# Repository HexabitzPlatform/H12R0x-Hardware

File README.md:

# H12R0x-Hardware
Hexabitz Industrial 12-Bit Analog Input ±10 V Module Hardware Design

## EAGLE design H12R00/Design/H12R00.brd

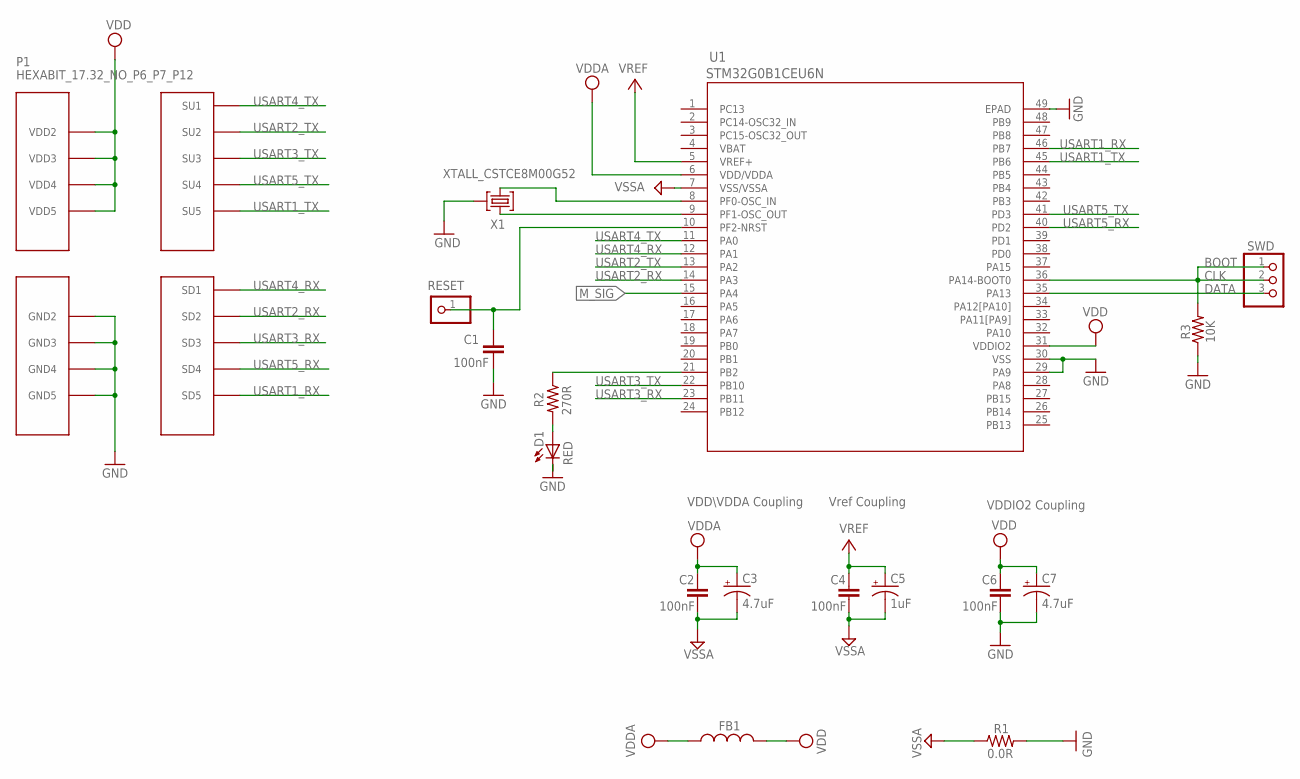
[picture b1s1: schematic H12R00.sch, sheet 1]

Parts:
C1, C2, C4, C6: 100nF; C-0603
C3, C7: 4.7uF; C-0805-POL
C5: 1uF; C-0805-POL
D1: RED; VLMS1300-GS08; MPN VLMS1300-GS08
FB1: FB-0603
P1: HEXABIT_17.32_NO_P6_P7_P12
R1: 0.0R; R-0603
R2: 270R; R-0603
R3: 10K; R-0603
RESET: R; 1X01
SWD: PINHD-1X3SWD; SWD
U1: STM32G0B1CEU6N; HEXABITZ_ICS_QFN_B1CEU6_STM-L
X1: XTALL_CSTCE8M00G52

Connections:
CLK: R3.2, SWD.1, SWD.2, U1.36 (PA14-BOOT0)
DATA: SWD.3, U1.35 (PA13)
GND: C1.2, C6.2, C7.2 (-), D1.C, P1.PAD_PD8 (GND2), P1.PAD_PD9 (GND3), P1.PAD_PD10 (GND4), P1.PAD_PD11 (GND5), R1.2, R3.1, U1.29 (PA9), U1.30 (VSS), U1.49 (EPAD), X1.P$2 (2)
M_SIG: U1.15 (PA4); also elsewhere on the board
unnamed: D1.A, R2.2
unnamed: R2.1, U1.21 (PB2)
unnamed: U1.9 (PF1-OSC_OUT), X1.P$1 (1)
unnamed: U1.8 (PF0-OSC_IN), X1.P$3 (3)
unnamed: C1.1, RESET.1, U1.10 (PF2-NRST)
USART1_RX: P1.PAD_PD5 (SD5), U1.46 (PB7)
USART1_TX: P1.PAD_PU5 (SU5), U1.45 (PB6)
USART2_RX: P1.PAD_PD2 (SD2), U1.14 (PA3)
USART2_TX: P1.PAD_PU2 (SU2), U1.13 (PA2)
USART3_RX: P1.PAD_PD3 (SD3), U1.23 (PB11)
USART3_TX: P1.PAD_PU3 (SU3), U1.22 (PB10)
USART4_RX: P1.PAD_PD1 (SD1), U1.12 (PA1)
USART4_TX: P1.PAD_PU1 (SU1), U1.11 (PA0)
USART5_RX: P1.PAD_PD4 (SD4), U1.40 (PD2)
USART5_TX: P1.PAD_PU4 (SU4), U1.41 (PD3)
VBAT: U1.4 (VBAT)
VDD: C6.1, C7.1 (+), FB1.2, P1.PAD_PU8 (VDD2), P1.PAD_PU9 (VDD3), P1.PAD_PU10 (VDD4), P1.PAD_PU11 (VDD5), U1.31 (VDDIO2)
VDDA: C2.1, C3.1 (+), FB1.1, U1.6 (VDD/VDDA); also elsewhere on the board
VREF: C4.1, C5.1 (+), U1.5 (VREF+); also elsewhere on the board
VSSA: C2.2, C3.2 (-), C4.2, C5.2 (-), R1.1, U1.7 (VSS/VSSA); also elsewhere on the board

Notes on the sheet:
Vref Coupling
VDDIO2 Coupling
VDD\VDDA Coupling
BOOT

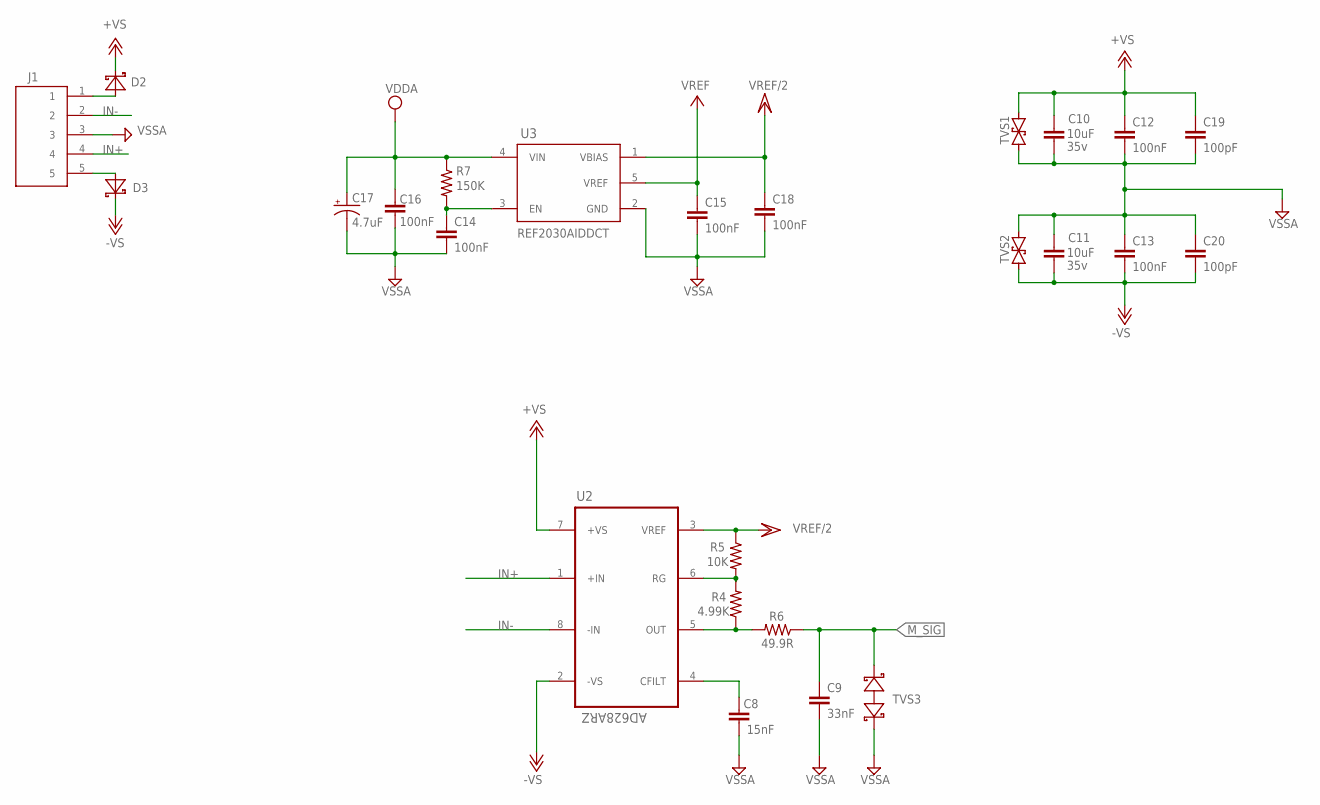
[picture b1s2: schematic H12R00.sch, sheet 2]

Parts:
C8: 15nF; C-0603
C9: 33nF; C-0603
C10, C11: C-0805; VOLTAGE_RATING 35v; MPN GRM21BR6YA106ME43K
C12, C13: 100nF; C-0603; MPN C1608X7R1H104K080AA
C14, C15, C16, C18: 100nF; C-0603
C17: 4.7uF; C-0805-POL
C19, C20: 100pF; C-0603; MPN C1608X7R1H104K080AA
D2, D3: DIOD-SOD-123; SOD123
J1: 1984646
R4: 4.99K; R-0603
R5: 10K; R-0603
R6: 49.9R; R-0603
R7: 150K; R-0603
TVS1, TVS2: SMBJ30CA; DO214AA
TVS3: BOURNS_CDSOD323-T03SCBOURNS_CDSOD323-T03SC_0_0; BOURNS_CDSOD323-T03SC_0
U2: AD628ARZ; SOIC127P600X175-8N
U3: TEXAS_INSTRUMENTS_REF2033AIDDCRTEXAS_INSTRUMENTS_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; TEXAS_INSTRUMENTS_REF2033AIDDCR_2; MPN REF2030AIDDCT

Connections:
+VS: C10.1, C12.1, C19.1, D2.2 (C), TVS1.C (2), U2.7 (+VS)
-VS: C11.2, C13.2, C20.2, D3.2 (C), TVS2.A (1), U2.2 (-VS)
CFILT: C8.1, U2.4 (CFILT)
IN+: J1.4, U2.1 (+IN)
IN-: J1.2, U2.8 (-IN)
M_SIG: C9.1, R6.1, TVS3.2 (C); also elsewhere on the board
unnamed: D3.1 (A), J1.5
unnamed: D2.1 (A), J1.1
unnamed: C14.1, R7.2, U3.3 (EN)
OUT: R4.1, R6.2, U2.5 (OUT)
RG: R4.2, R5.2, U2.6 (RG)
VDDA: C16.1, C17.1 (+), R7.1, U3.4 (VIN); also elsewhere on the board
VREF: C15.1, U3.5 (VREF); also elsewhere on the board
VREF/2: C18.1, R5.1, U2.3 (VREF), U3.1 (VBIAS)
VSSA: C8.2, C9.2, C10.2, C11.1, C12.2, C13.1, C14.2, C15.2, C16.2, C17.2 (-), C18.2, C19.2, C20.1, J1.3, TVS1.A (1), TVS2.C (2), TVS3.1 (A), U3.2 (GND); also elsewhere on the board

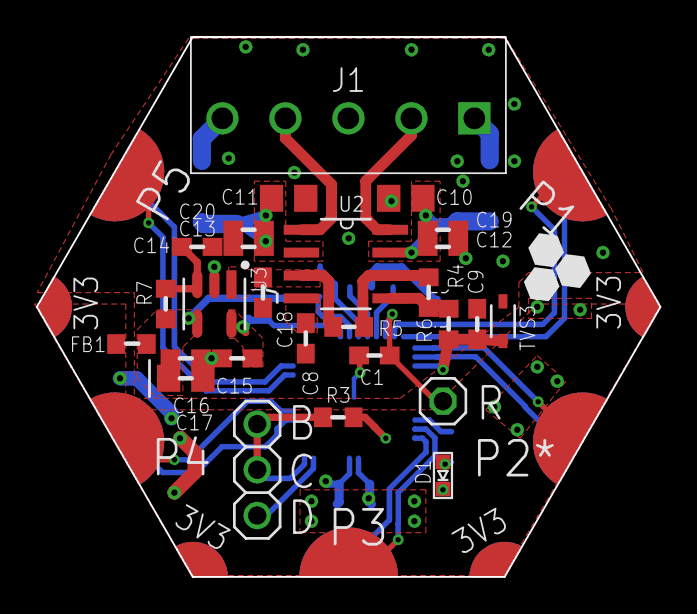
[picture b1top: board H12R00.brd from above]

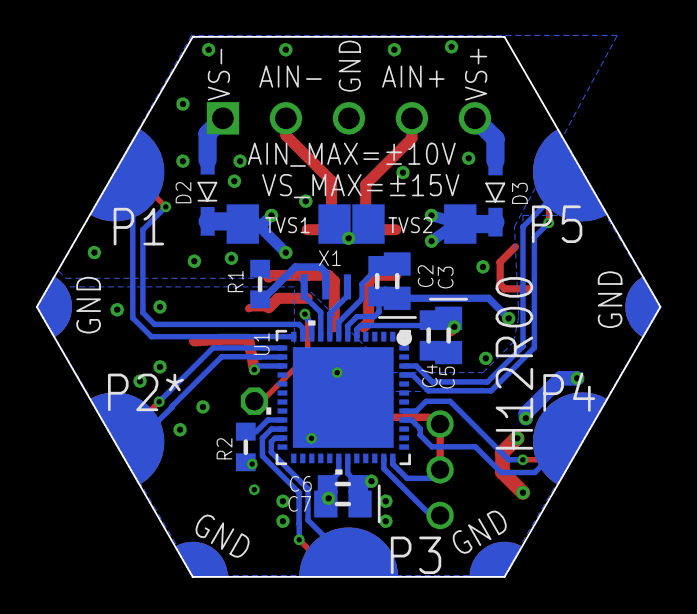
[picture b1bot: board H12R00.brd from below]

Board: 2 copper layers, 34.6 x 30.0 mm, 42 parts (14 on the bottom side), 34 nets.

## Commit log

2020-03-16 Adding template files
2020-03-16 in this commit:
    - schematic is ready
    - PCB is ready
    - All output files were generated
2020-03-18 - replaced connectors and redrawn PCB (output files were not updated)
2020-03-18 minor modifications on res names placements
2020-03-29 changed schematic design and modifies PCB (output files were not updated)
2020-04-07 PCB modifications and output files were generated
2020-04-24 Update some components from lib. REF is missing in lib
2020-04-25 Update REF from library Fix routing and DRC issues
2020-04-25 Review ERC/DRC Generate gerber, drill, schematics pdf and pick n place Update BOM Release V0
2020-04-25 remove temp files
2020-05-23 Fix some BOM errors
2020-12-28 - Fixed C11 and C14 attributes..
2021-09-06 - Fixed labels in .sch and .brd from 12v to 10v - Regenerated docoument file - Fixed BOM - Regenerated output files (Gerber, drills, mount)
2021-09-24 - Made some Hardware modifications (.sch and .brd where updated) - Updated Documentation - Updated BOM - Regenerated output files
2023-10-29 -First commit after the mass editing (before start wiring) : 1- Edit the design so the module can measure the pos & neg sides of the analog input signal . 2 - Change the MCU to stm32g0b1ceu6n
2023-10-29 -After wiring
2023-10-30 -All done
2023-11-05 - Fix some documentation issues
2023-11-05 -Fix BOM

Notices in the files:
parts and their libraries:
HEXABITZ_ICs: COPYRIGHT: Copyright (C) 2022 Ultra Librarian. All rights reserved.
